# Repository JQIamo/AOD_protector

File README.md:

# AOD Protector
The protection circuit for the acousto-optic deflectors used for tweezers.

This KiCad project contains the following parts:

- [Main board](#main-board) (`AOD_protector-main`): the main board detecting and thresholding a single-channel rf signal
- [Fault handler](#fault-handler) (`AOD_protector-fault_handler`): a board to output a LVTTL flag to indicate a triggered incident
- [Power board](#power-board) (`AOD_protector-power_board`): the power regulating and distributing board (used in company with a switching AC-DC block)
- (optional) [Bandpass filter](#bandpass-filter-optional) (`AOD_protector-BPF_testboard`): bandpass filters to restrict the signal within a designated spectral band

Additionally, we made a custom CNC design based on Cheval's HS19AL1UD2 rack mount box. The design files can be found under `rack-mount_box`.

## Main board
The board is designed to implement an rf switch controlled by a power detector so the circuit is broken when the rf power is above a threshold. The input signal goes through a sampling circuit and enters the rf switch (QPC6014TR7) before going to the output.

The sampling circuit diverts $3.85~\%$ of the total power into the detection chip (ADL5511ACPZ-R7) which has a $250~\Omega$ input impedance. For low frequency (\~ $100\textrm{ MHz}$) signals, the $V_{rms}$ output of the chip is $V_{rms}=1.92\overline{V_{in}}+11\textrm{ mV}$. The $\overline{V_{in}}$ is the averaged voltage of the input low-pass filtered over a corner frequency determined by the capacitor connected to pin `FLT4`: $f_{LP}=1/(800 \pi\ \Omega~(C_{FLT4}+20\textrm{ pF}))$. In our case with $C_{FLT4}=470\textrm{ pF}$, $f_{LP}=812\textrm{ kHz}$.

The output of the chip is fed into a comparator (MAX9141ESA+) whose inverting input is set by a voltage reference and a variable voltage divider. With all the components taken into consideration, we have $V_{th}\ge0.384\overline{V_{in}}+10.5\textrm{ mV}$, and the trimpot should allow us to tune the threshold of the rf power from $-7\textrm{ dBm}$ to $2\textrm{ dBm}$ measured at the power divider. The remaining circuit and the rf switch will contribute an additional insertion loss of around $0.8\textrm{ dB}$ at low rf frequency. It is worth noting that the estimated total insertion loss is around $0.98\textrm{ dB}$.

When the voltage goes beyond the threshold, the comparator will engage a latch, disable the rf switch, send a flag to the fault-handler board, and turn on the on-board red LED. The status of the comparator can be reset by the pushbutton manually.

### *Change the threshold range*
The threshold's dynamic range can be adjusted by changing the resistors R3, R6, and the potentiometer RV1. The three resistors together form a voltage divider that outputs the desired $V_{th}$ from the $1.024~\textrm{V}$ voltage reference.

Together with the discussion about the rf power, $V_{th}$, and insertion loss in the previous paragraphs, the rf power threshold measured at the output port in dBm can be derived as follows:

$$20\log_{10}\left(10.24\frac{R_6+RV_1}{R_3+R_6+RV_1}-0.105\right)\textrm{ dBm}+0.52\textrm{ dBm}$$

## Fault handler

The fault handler board collectively receives the flag from the 4 main boards with an OR logic. When there is an over-threshold incident occurs on one of the main boards, the anode voltage of the optocoupler (TLP2767) will be pulled down and a $3.3\textrm{ V}$ voltage will be sent to the output BNC connector.

## Power board
The power board filters the input 5V DC power line from a switching AC-DC adapter and distributes it to multiple boards. The filtering circuit is adapted from the [Jane](https://github.com/JQIamo/jane.git) project (for the KiCad version of the design, contact Alessandro Restelli).

## Bandpass filter (optional)
Ideally we want to implement a bandpass filter to suppress signals outside the operational bandwidth of the AOD for safety. With that in mind I designed a 5-order Butterworth bandpass filter for the two kinds of AOD we use respectively. Please refer to the Qucs file and board design for the details.

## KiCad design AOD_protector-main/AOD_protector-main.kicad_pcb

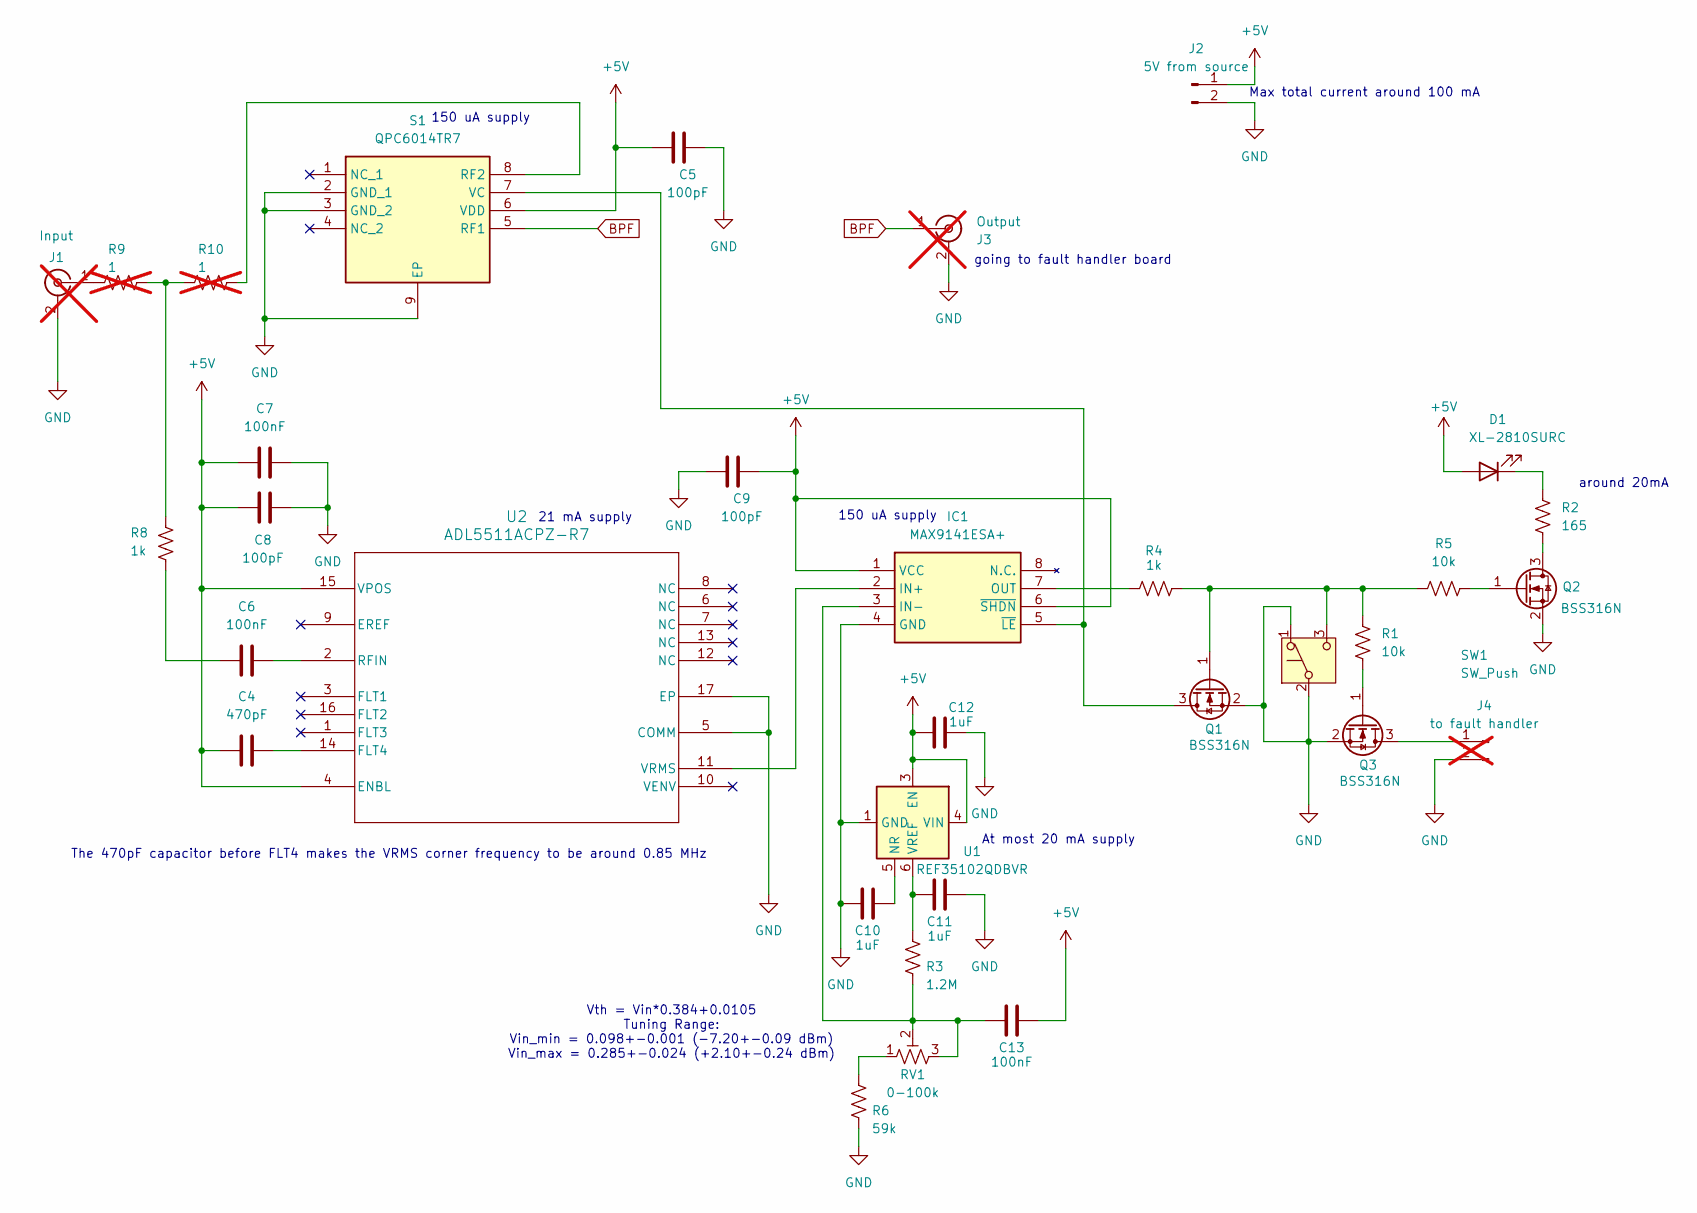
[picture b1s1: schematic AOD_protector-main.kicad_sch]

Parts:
C4: 470pF; C_0402_1005Metric; Part number CC0402FRNPO9BN471; JLCPCB Part C513551
C5, C8, C9: 100pF; C_0402_1005Metric; Part number CC0402FRNPO9BN101; JLCPCB Part C327198
C6, C7, C13: 100nF; C_0603_1608Metric; Part number CC0603JRX7R9BB104; JLCPCB Part C91183
C10, C11, C12: 1uF; C_0603_1608Metric; Part number CL10B105KB8NQNC; JLCPCB Part C5199872
D1: XL-2810SURC; LED-SMD_L3.5-W1.4-FD-1; Part number XL-2810SURC; JLCPCB Part C3646948
IC1: MAX9141ESA+; SOIC127P600X175-8N; Manufacturer_Part_Number MAX9141ESA+; Mouser Part Number 700-MAX9141ESA
J1: Input; BNC_Amphenol_031-6233_EdgeMount; Part number 031-6233; not fitted
J2: 5V from source; CONN-TH_2P-P2.54_MX128-2.54-GN01-02P-CU-Y-A; Part number MX128-2.54-02P-GN01-Cu-Y-A; JLCPCB Part C5188442
J3: Output; BNC_Amphenol_031-6233_EdgeMount; Part number 031-6233; not fitted
J4: to fault handler; PinHeader_1x02_P2.54mm_Vertical; not fitted
Q1, Q2, Q3: BSS316N; SOT-23; Part number BSS316N; JLCPCB Part C19829413
R1, R5: 10k; R_0402_1005Metric; Part number RT0402BRD0710KL; JLCPCB Part C190095
R2: 165; R_0603_1608Metric; Part number ARG03BTC1650; JLCPCB Part C5266122
R3: 1.2M; R_0603_1608Metric; Part number MCT0603MD1204BP500; JLCPCB Part C3933664
R4, R8: 1k; R_0402_1005Metric; Part number RT0402BRD071KL; JLCPCB Part C852624
R6: 59k; R_0402_1005Metric; Part number RT0402BRD0759KL; JLCPCB Part C852853
R9, R10: 1; R_0402_1005Metric; not fitted
RV1: 0-100k; RES-ADJ-TH_3296X; Part number 3296X-1-104LF; JLCPCB Part C49473
S1: QPC6014TR7; SON50P200X200X90-9N-D; Manufacturer_Part_Number QPC6014TR7; Mouser Part Number 772-QPC6014TR7
SW1: SW_Push; SW-TH_TK-6580B-2; Part number TK-6580B-2; JLCPCB Part C2689830
U1: REF35102QDBVR; SOT-23-6; Part number REF35102QDBVR; JLCPCB Part C6265001
U2: ADL5511ACPZ-R7; CP_16_22_ADI; Part number ADL5511ACPZ-R7; JLCPCB Part C579159

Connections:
+5V: C4.1, C5.1, C7.1, C8.1, C9.2, C12.2, C13.1, D1.2 (A), IC1.1 (VCC), IC1.6 (~SHDN), J2.1, S1.6 (VDD), U1.3 (EN), U1.4 (VIN), U2.4 (ENBL), U2.15 (VPOS)
BPF: J3.1 (In), S1.5 (RF1)
GND: C5.2, C7.2, C8.2, C9.1, C10.2, C11.1, C12.1, IC1.4 (GND), J1.2 (Ext), J2.2, J3.2 (Ext), J4.2, Q1.2 (S), Q2.2 (S), Q3.2 (S), R6.1, S1.2 (GND_1), S1.3 (GND_2), S1.9 (EP), SW1.1 (A), SW1.2 (B), U1.1 (GND), U1.2 (GND), U2.5 (COMM), U2.17 (EP)
unnamed: C6.1, R8.1
unnamed: D1.1 (K), R2.1
unnamed: IC1.2 (IN+), U2.11 (VRMS)
unnamed: C13.2, IC1.3 (IN-), R3.1, RV1.2, RV1.3
unnamed: IC1.7 (OUT), R4.1
unnamed: IC1.5 (~LE), Q1.3 (D), S1.7 (VC)
unnamed: J1.1 (In), R9.1
unnamed: J4.1, Q3.3 (D)
unnamed: Q1.1 (G), R1.1, R4.2, R5.2, SW1.3 (C)
unnamed: Q2.3 (D), R2.2
unnamed: Q2.1 (G), R5.1
unnamed: Q3.1 (G), R1.2
unnamed: R6.2, RV1.1
unnamed: R8.2, R9.2, R10.1
unnamed: R10.2, S1.8 (RF2)
unnamed: C10.1, U1.5 (NR)
unnamed: C11.2, R3.2, U1.6 (VREF)
unnamed: C4.2, U2.14 (FLT4)
unnamed: C6.2, U2.2 (RFIN)

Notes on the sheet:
At most 20 mA supply
21 mA supply
150 uA supply
Vth = Vin*0.384+0.0105 Tuning Range: Vin_min = 0.098+-0.001 (-7.20+-0.09 dBm) Vin_max = 0.285+-0.024 (+2.10+-0.24 dBm)
around 20mA
going to fault handler board
Max total current around 100 mA
The 470pF capacitor before FLT4 makes the VRMS corner frequency to be around 0.85 MHz

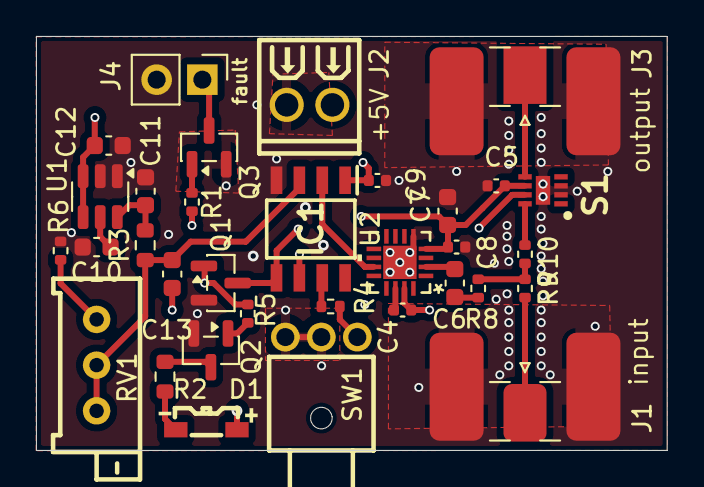
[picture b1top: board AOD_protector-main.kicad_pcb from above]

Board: 4 copper layers, 35.0 x 23.0 mm, 33 parts (0 on the bottom side), 22 nets.

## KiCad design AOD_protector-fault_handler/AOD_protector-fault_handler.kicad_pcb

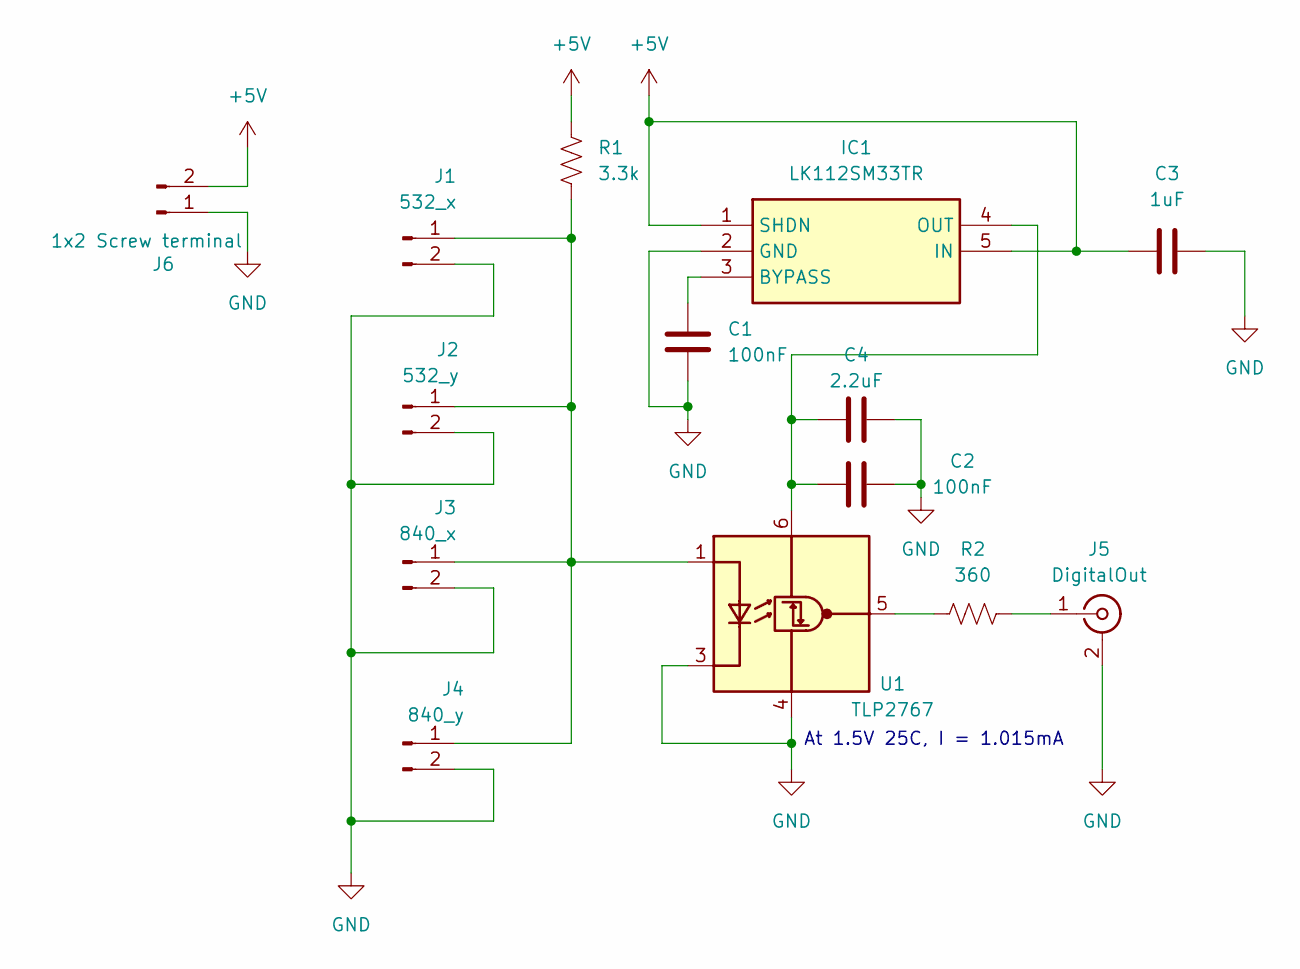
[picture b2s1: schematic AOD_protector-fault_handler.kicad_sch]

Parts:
C1, C2: 100nF; C_0603_1608Metric
C3: 1uF; C_0805_2012Metric
C4: 2.2uF; C_0805_2012Metric
IC1: LK112SM33TR; SOT95P280X145-5N; Mouser Part Number 511-LK112SM33
J1: 532_x; PinHeader_1x02_P2.54mm_Vertical
J2: 532_y; PinHeader_1x02_P2.54mm_Vertical
J3: 840_x; PinHeader_1x02_P2.54mm_Vertical
J4: 840_y; PinHeader_1x02_P2.54mm_Vertical
J5: DigitalOut; BNC_Amphenol_031-6233_EdgeMount; Manufacturer_Part_Number 031-6233
J6: 1x2 Screw terminal; CONN-TH_2P-P2.54_MX128-2.54-GN01-02P-CU-Y-A
R1: 3.3k; R_0603_1608Metric
R2: 360; R_0603_1608Metric
U1: TLP2767; SO-6L_10x3.84mm_P1.27mm; Manufacturer_Part_Number TLP2767

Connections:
+5V: C3.1, IC1.1 (SHDN), IC1.5 (IN), J6.2, R1.1
GND: C1.2, C2.2, C3.2, C4.2, IC1.2 (GND), J1.2, J2.2, J3.2, J4.2, J5.2 (Ext), J6.1, U1.3 (K), U1.4 (GND)
unnamed: C1.1, IC1.3 (BYPASS)
unnamed: C2.1, C4.1, IC1.4 (OUT), U1.6 (VDD)
unnamed: J1.1, J2.1, J3.1, J4.1, R1.2, U1.1 (A)
unnamed: J5.1 (In), R2.2
unnamed: R2.1, U1.5 (VO)

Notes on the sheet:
At 1.5V 25C, I = 1.015mA

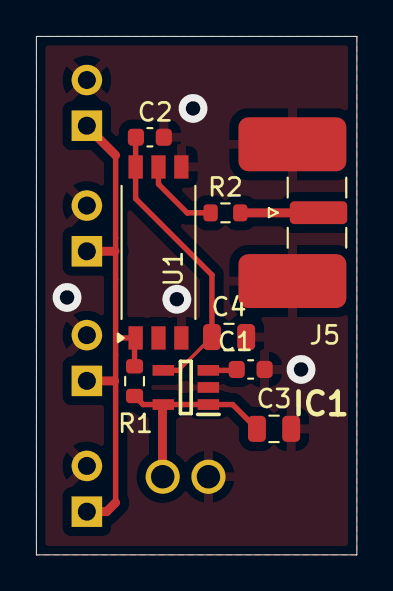
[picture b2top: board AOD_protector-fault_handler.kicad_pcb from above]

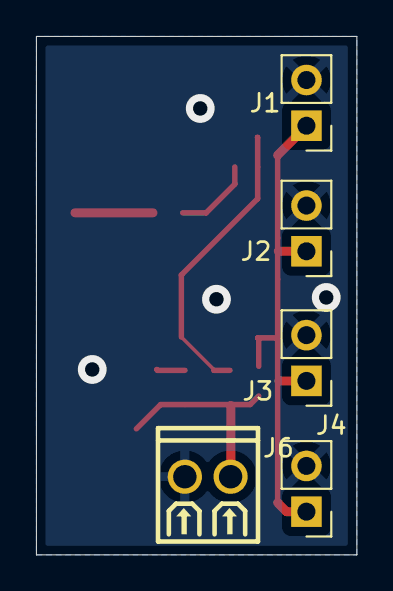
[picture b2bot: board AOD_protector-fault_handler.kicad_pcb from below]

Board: 2 copper layers, 17.8 x 28.8 mm, 14 parts (5 on the bottom side), 7 nets.

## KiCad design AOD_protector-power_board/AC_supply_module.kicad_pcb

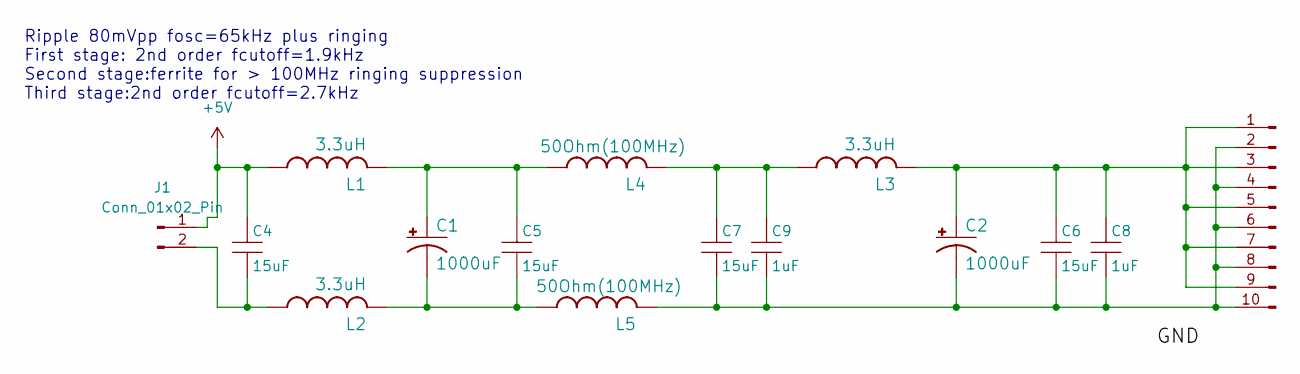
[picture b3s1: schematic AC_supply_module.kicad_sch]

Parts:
C1, C2: 1000uF; E3,5-8; PARTNO APSG160ELL102MH20S; DIGIKEY 565-4311-ND
C4, C5, C6, C7: 15uF; C_MLCC_0805; PARTNO C2012JB1E156M125AC; DIGIKEY 445-11470-1-ND
C8, C9: 1uF; C_MLCC_0306; PARTNO C0816X5R1C105M050AC; DIGIKEY 445-13750-1-ND
J1: Conn_01x02_Pin; TerminalBlock_Phoenix_PT-1,5-2-3.5-H_1x02_P3.50mm_Horizontal; Manufacturer_Part_Number DB301V-3.5-2P-GN-S
J2: Conn_01x08_Pin; TerminalBlock_Phoenix_PT-1,5-10-3.5-H_1x10_P3.50mm_Horizont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; Manufacturer_Part_Number DB125-3.5-8P-GN-S
L1, L2, L3: 3.3uH; L-322X322; PARTNO IHLP3232DZER3R3M11; DIGIKEY 541-1352-1-ND
L4, L5: 50Ohm(100MHz); C1206; PARTNO BLM31SN500SN1L; DIGIKEY 490-13269-1-ND

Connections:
+5V: C4.P$1 (1), J1.1, L1.P$1 (1)
unnamed: C4.P$2 (2), J1.2, L2.P$1 (1)
unnamed: C1.+, C5.P$1 (1), L1.P$2 (2), L4.1
unnamed: C1.-, C5.P$2 (2), L2.P$2 (2), L5.1
unnamed: C2.+, C6.P$1 (1), C8.P$1 (1), J2.1, J2.3, J2.5, J2.7, J2.9, L3.P$2 (2)
unnamed: C2.-, C6.P$2 (2), C7.P$2 (2), C8.P$2 (2), C9.P$2 (2), J2.2, J2.4, J2.6, J2.8, J2.10, L5.2
unnamed: C7.P$1 (1), C9.P$1 (1), L3.P$1 (1), L4.2

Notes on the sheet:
Ripple 80mVpp fosc=65kHz plus ringing First stage: 2nd order fcutoff=1.9kHz Second stage:ferrite for > 100MHz ringing suppression Third stage:2nd order fcutoff=2.7kHz

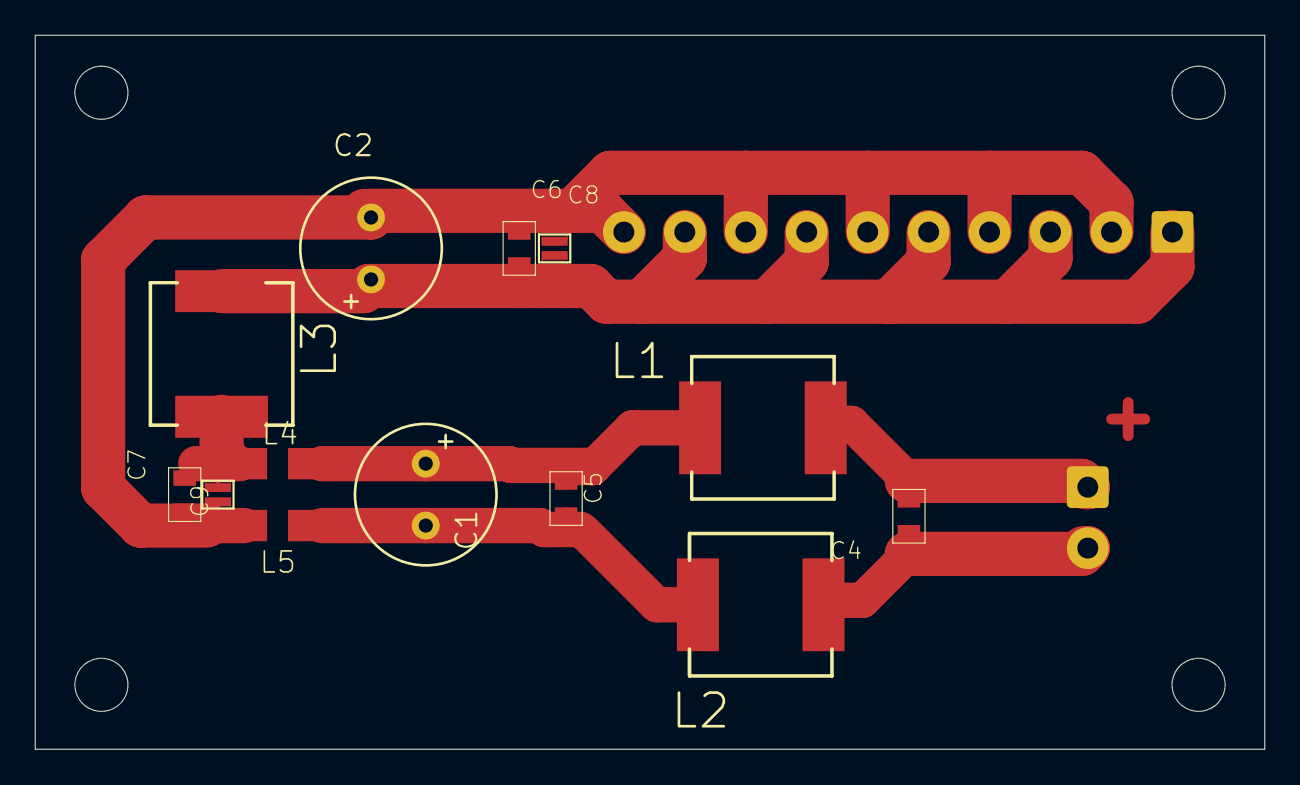
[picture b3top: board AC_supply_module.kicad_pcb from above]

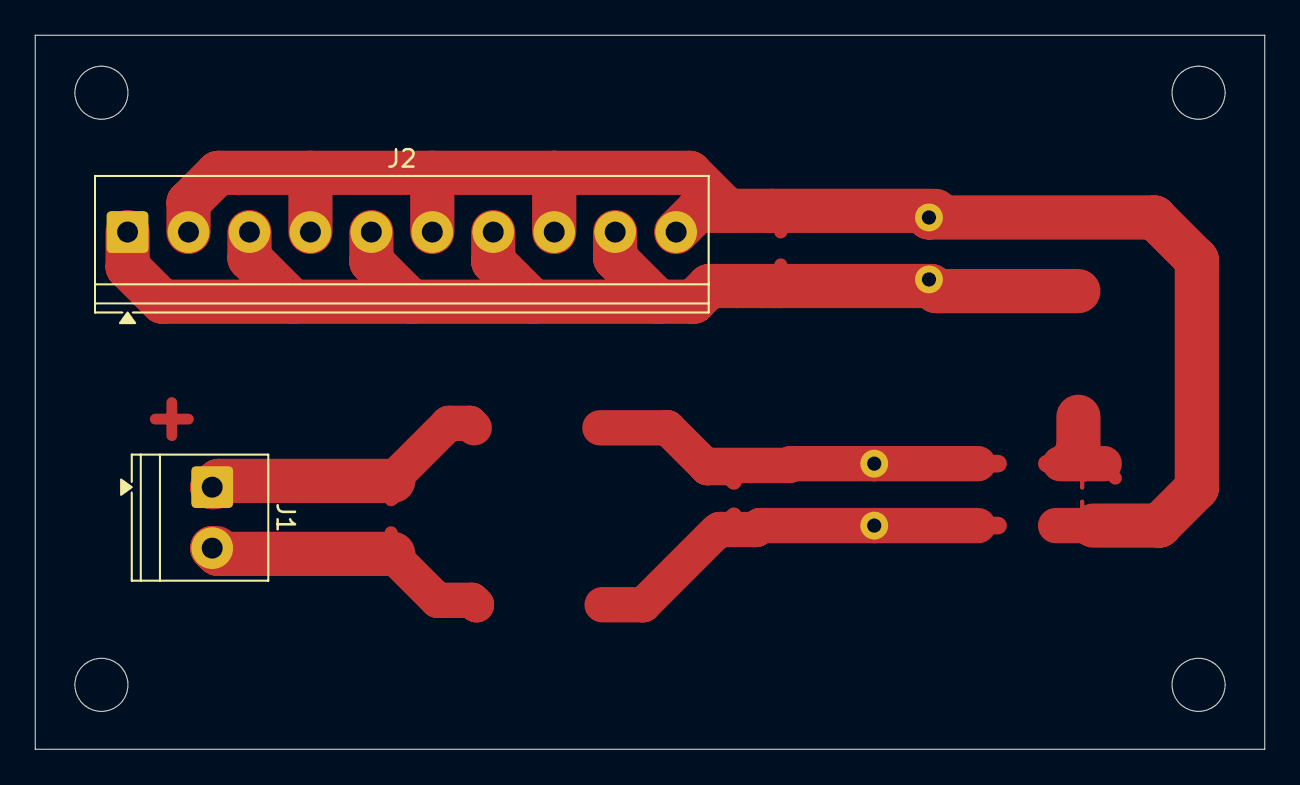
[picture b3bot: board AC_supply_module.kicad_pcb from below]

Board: 2 copper layers, 70.6 x 41.0 mm, 17 parts (2 on the bottom side), 7 nets.

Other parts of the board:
@HOLE1, @HOLE2: (no value)

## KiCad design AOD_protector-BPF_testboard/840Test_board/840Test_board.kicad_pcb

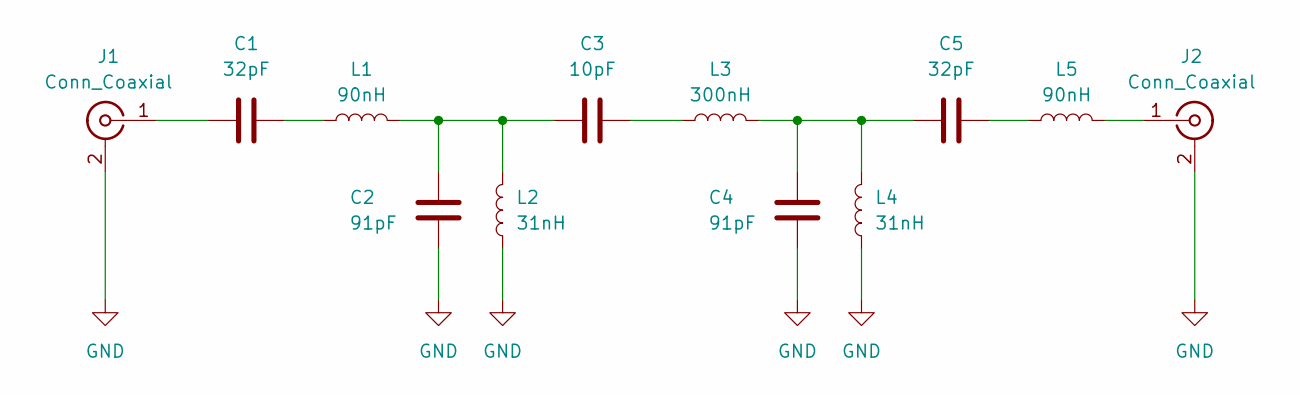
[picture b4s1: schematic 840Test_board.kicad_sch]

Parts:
C1, C5: 32pF; C_0603_1608Metric; Part Number 06031A320FAT2A
C2, C4: 91pF; C_0402_1005Metric; Part Number GRT1555C1H910FA02D
C3: 10pF; C_0402_1005Metric; Part Number 04025U100BAT2A
J1, J2: Conn_Coaxial; BNC_Amphenol_031-6233_EdgeMount; Part Number 031-6233
L1, L5: 90nH; AC1060R90NG; Part Number AC1060R-90NG
L2, L4: 31nH; L_0603_1608Metric; Part Number LQW18AN31NG8ZD
L3: 300nH; 2222SQ301GEC; Part Number 2222SQ301GEC

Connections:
GND: C2.1, C4.1, J1.2 (Ext), J2.2 (Ext), L2.1, L4.1
unnamed: C1.2, L1.1
unnamed: C2.2, C3.1, L1.2, L2.2
unnamed: C3.2, L3.1
unnamed: C4.2, C5.1, L3.2, L4.2
unnamed: C5.2, L5.1
unnamed: C1.1, J1.1 (In)
unnamed: J2.1 (In), L5.2

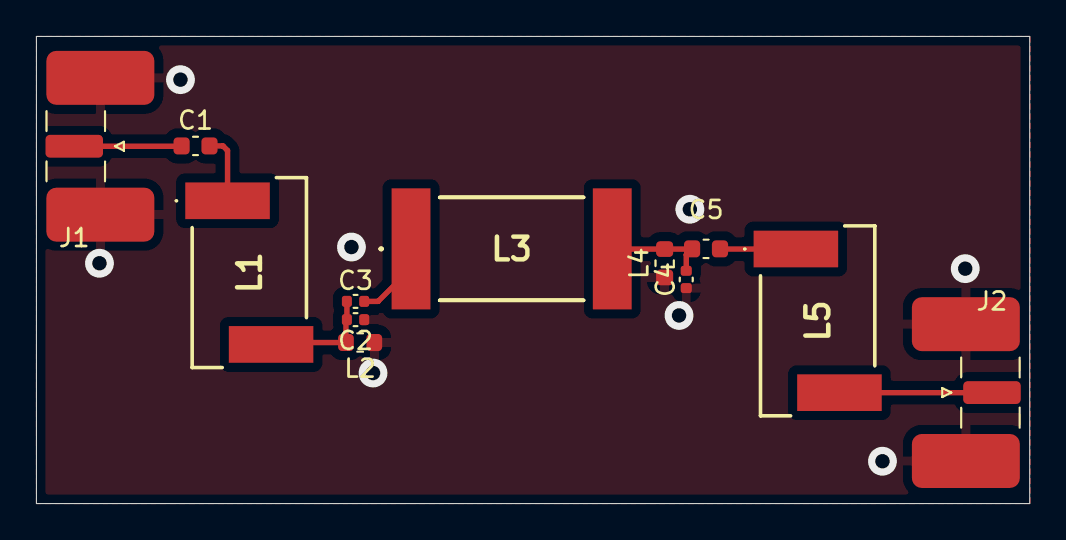
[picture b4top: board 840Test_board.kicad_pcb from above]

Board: 2 copper layers, 55.2 x 26.0 mm, 12 parts (0 on the bottom side), 8 nets.

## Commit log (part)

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2025-11-17 Init commit
2025-11-24 Fixed a resistor value bug
2025-12-09 Update with the rack-mount box designs
